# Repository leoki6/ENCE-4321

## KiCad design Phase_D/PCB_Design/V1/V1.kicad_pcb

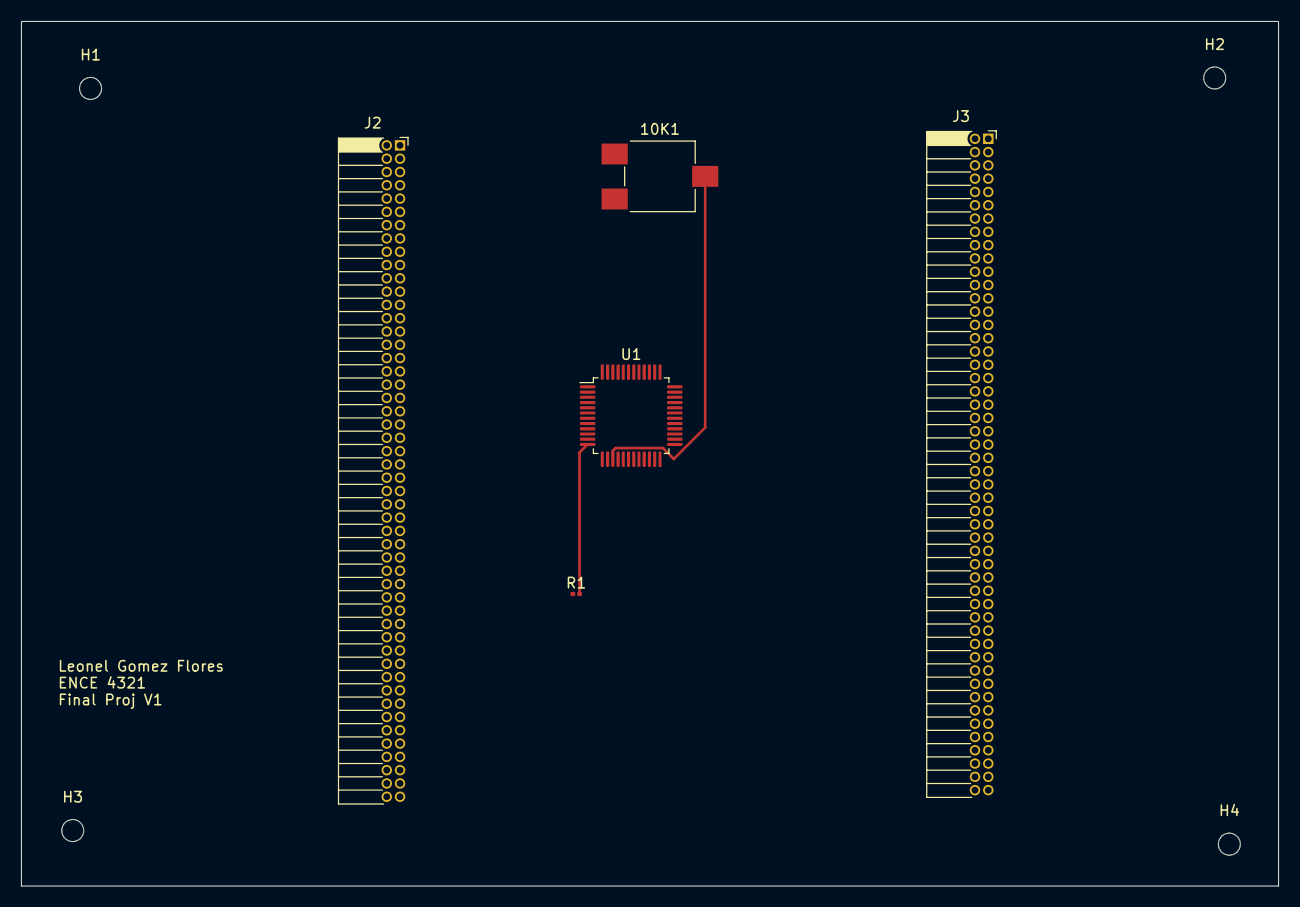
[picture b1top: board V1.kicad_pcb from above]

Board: 2 copper layers, 120.1 x 82.6 mm, 9 parts (0 on the bottom side), 2 nets.

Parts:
10K1: R_Potentiometer; Potentiometer_ACP_CA6-VSMD_Vertical
H1, H2, H3, H4: MountingHole; MountingHole_2.1mm
J2, J3: Conn_01x40_Socket; PinSocket_2x50_P1.27mm_Horizontal
R1: R; R_0201_0603Metric
U1: STM32C031C4Tx; LQFP-48_7x7mm_P0.5mm

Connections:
ADC_1: R1.2, U1.12 (PA1)
ADC_2: 10K1.2, U1.15 (PA4)

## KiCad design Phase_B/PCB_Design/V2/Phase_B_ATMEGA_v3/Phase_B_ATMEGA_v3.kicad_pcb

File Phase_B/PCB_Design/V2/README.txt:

The initial version of the folder Phase_B_ATMEGA_v3 was a template provided by Professor Martins
in ENCE-4231.

Files pertaining to the generation/creation of: housing, component placement, PCB dimensioning, Drill, Gerber, 3D Models, etc
were created by the author of this repository.

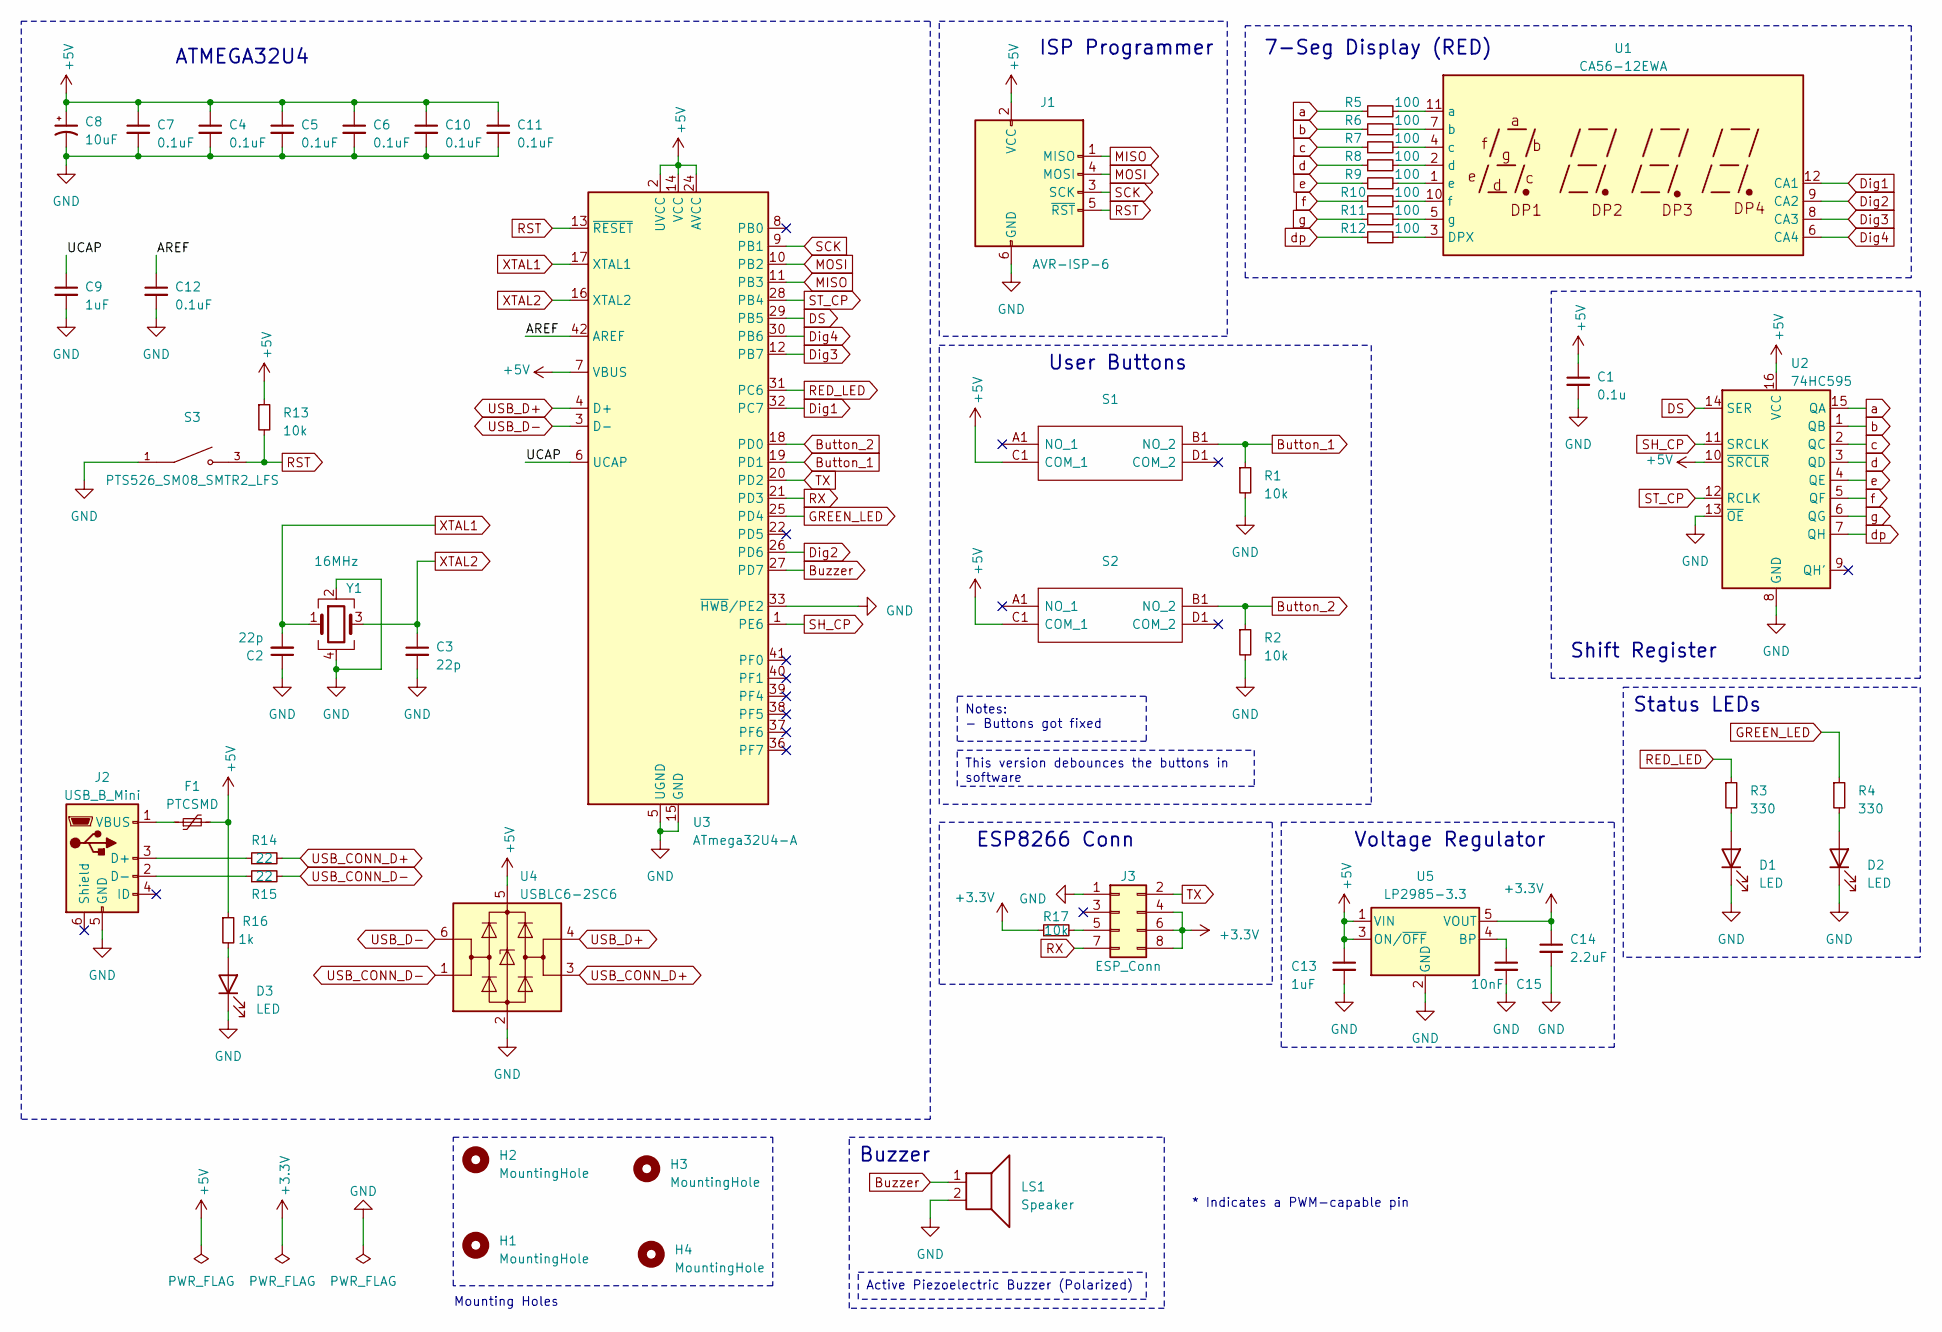
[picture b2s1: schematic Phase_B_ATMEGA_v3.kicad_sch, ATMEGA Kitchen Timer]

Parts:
C1: 0.1u; C_0603_1608Metric
C2, C3: 22p; C_0603_1608Metric
C4, C5, C6, C7, C10, C11, C12: 0.1uF; C_0603_1608Metric
C8: 10uF; C_0805_2012Metric
C9, C13: 1uF; C_0603_1608Metric
C14: 2.2uF; C_0603_1608Metric
C15: 10nF; C_0603_1608Metric
D1, D2, D3: LED; LED_0805_2012Metric
F1: PTCSMD; Fuse_1812_4532Metric
H1, H2, H3, H4: MountingHole; MountingHole_2.2mm_M2
J1: AVR-ISP-6; PinSocket_2x03_P2.54mm_Vertical
J2: USB_B_Mini; USB_Mini-B_Lumberg_2486_01_Horizontal
J3: ESP_Conn; PinSocket_2x04_P2.54mm_Vertical
LS1: Speaker; Buzzer_12x9.5RM7.6
R1, R2: 10k; R_0805_2012Metric
R3, R4: 330; R_0805_2012Metric
R5, R6, R7, R8, R9, R10, R11, R12: 100; R_0805_2012Metric
R13, R17: 10k; R_0603_1608Metric
R14, R15: 22; R_0603_1608Metric
R16: 1k; R_0603_1608Metric
S1, S2: PTS125SM43SMTR21M_LFS; PTS125_SMD_Button; Manufacturer_Part_Number PTS125SM43SMTR21M LFS; Mouser Part Number 611-PTS125S43SMTRLFS
S3: PTS526_SM08_SMTR2_LFS; PTS526_SMD_Button; PARTREV 20 mar 19
U1: CA56-12EWA
U2: 74HC595; TSSOP-16_4.4x5mm_P0.65mm
U3: ATmega32U4-A; TQFP-44_10x10mm_P0.8mm
U4: USBLC6-2SC6; SOT-23-6
U5: LP2985-3.3; SOT-23-5
Y1: 16MHz; Crystal_SMD_Abracon_ABM8G-4Pin_3.2x2.5mm

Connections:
+3.3V: C14.1, J3.4, J3.6, J3.8, R17.1, U5.5 (VOUT)
+5V: C1.1, C4.1, C5.1, C6.1, C7.1, C8.1, C10.1, C11.1, C13.1, F1.2, J1.2 (VCC), R13.1, R16.1, S1.C1 (COM_1), S2.C1 (COM_1), U2.10 (~SRCLR), U2.16 (VCC), U3.2 (UVCC), U3.7 (VBUS), U3.14 (VCC), U3.24 (AVCC), U3.34 (VCC), U3.44 (AVCC), U4.5 (VBUS), U5.1 (VIN), U5.3 (ON/~OFF)
/AREF: C12.1, U3.42 (AREF)
/UCAP: C9.1, U3.6 (UCAP)
Button_1: R1.1, S1.B1 (NO_2), U3.19 (PD1)
Button_2: R2.1, S2.B1 (NO_2), U3.18 (PD0)
Buzzer: LS1.1, U3.27 (PD7)
DS: U2.14 (SER), U3.29 (PB5)
Dig1: U1.12 (CA1), U3.32 (PC7)
Dig2: U1.9 (CA2), U3.26 (PD6)
Dig3: U1.8 (CA3), U3.12 (PB7)
Dig4: U1.6 (CA4), U3.30 (PB6)
GND: C1.2, C2.1, C3.2, C4.2, C5.2, C6.2, C7.2, C8.2, C9.2, C10.2, C11.2, C12.2, C13.2, C14.2, C15.2, D1.1 (K), D2.1 (K), D3.1 (K), J1.6 (GND), J2.5 (GND), J3.1, LS1.2, R1.2, R2.2, S3.1, U2.8 (GND), U2.13 (~OE), U3.5 (UGND), U3.15 (GND), U3.23 (GND), U3.33 (~HWB/PE2), U3.35 (GND), U3.43 (GND), U4.2 (GND), U5.2 (GND), Y1.2, Y1.4
GREEN_LED: R4.1, U3.25 (PD4)
MISO: J1.1 (MISO), U3.11 (PB3)
MOSI: J1.4 (MOSI), U3.10 (PB2)
unnamed: D1.2 (A), R3.2
unnamed: D2.2 (A), R4.2
unnamed: D3.2 (A), R16.2
unnamed: J2.3 (D+), R14.1
unnamed: J2.2 (D-), R15.1
unnamed: F1.1, J2.1 (VBUS)
unnamed: J3.5, R17.2
unnamed: R12.2, U1.3 (DPX)
unnamed: R5.2, U1.11 (a)
unnamed: R6.2, U1.7 (b)
unnamed: R7.2, U1.4 (c)
unnamed: R8.2, U1.2 (d)
unnamed: R9.2, U1.1 (e)
unnamed: R10.2, U1.10 (f)
unnamed: R11.2, U1.5 (g)
unnamed: C15.1, U5.4 (BP)
RED_LED: R3.1, U3.31 (PC6)
RST: J1.5 (~RST), R13.2, S3.3, U3.13 (~RESET)
RX: J3.7, U3.21 (PD3)
SCK: J1.3 (SCK), U3.9 (PB1)
SH_CP: U2.11 (SRCLK), U3.1 (PE6)
ST_CP: U2.12 (RCLK), U3.28 (PB4)
TX: J3.2, U3.20 (PD2)
USB_CONN_D+: R14.2, U4.3 (I/O2)
USB_CONN_D-: R15.2, U4.1 (I/O1)
USB_D+: U3.4 (D+), U4.4 (I/O2)
USB_D-: U3.3 (D-), U4.6 (I/O1)
XTAL1: C2.2, U3.17 (XTAL1), Y1.1
XTAL2: C3.1, U3.16 (XTAL2), Y1.3
a: R5.1, U2.15 (QA)
b: R6.1, U2.1 (QB)
c: R7.1, U2.2 (QC)
d: R8.1, U2.3 (QD)
dp: R12.1, U2.7 (QH)
e: R9.1, U2.4 (QE)
f: R10.1, U2.5 (QF)
g: R11.1, U2.6 (QG)

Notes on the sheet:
Notes: - Buttons got fixed
Active Piezoelectric Buzzer (Polarized)
This version debounces the buttons in software
Shift Register
Mounting Holes
Voltage Regulator
Status LEDs
ATMEGA32U4
User Buttons
Buzzer
* Indicates a PWM-capable pin
7-Seg Display (RED)
ISP Programmer
ESP8266 Conn

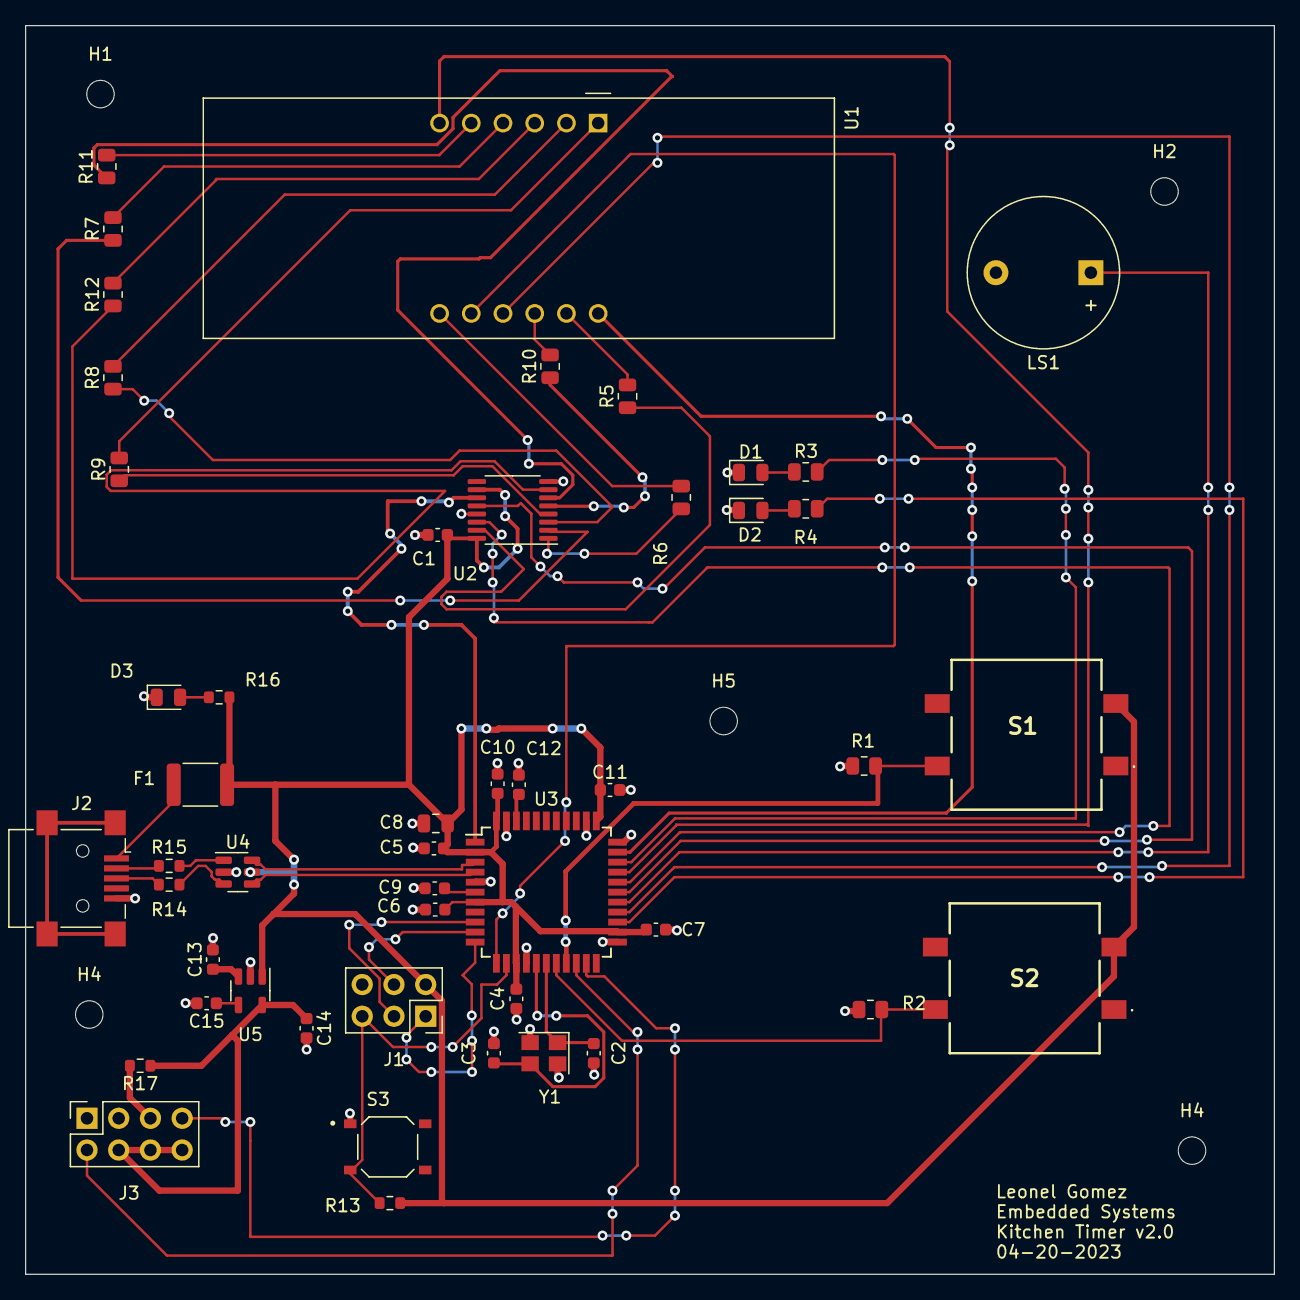
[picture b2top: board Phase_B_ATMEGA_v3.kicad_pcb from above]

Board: 2 copper layers, 100.0 x 100.0 mm, 54 parts (0 on the bottom side), 53 nets.

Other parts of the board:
H4#2, H5: MountingHole; MountingHole_2.2mm_M2

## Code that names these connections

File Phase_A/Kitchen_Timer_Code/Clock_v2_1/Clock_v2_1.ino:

#define BUTTON_2  2  // Inc Timer
#define BUTTON_1  3  // Start/Stop Timer and Stop Buzzer
#define GREEN_LED 4
#define RED_LED   5
#define BUZZER    6

#define DATA      9 // DS
#define LATCH     8 // ST_CP
#define CLOCK     7 // SH_CP

#define DIGIT_4   10
#define DIGIT_3   11
#define DIGIT_2   12
#define DIGIT_1   13

// 7-Seg Display Variables
unsigned char gtable[]=
{0x3f,0x06,0x5b,0x4f,0x66,0x6d,0x7d,0x07,0x7f,0x6f,0x77,0x7c
,0x39,0x5e,0x79,0x71,0x00};
byte gCurrentDigit;

// Volatile Variables
volatile unsigned char gISRFlag1   = 0;
volatile unsigned char gBuzzerFlag = 0;

// Timer Variables
#define DEFAULT_COUNT 30     // default value is 30secs
volatile int  gCount        = DEFAULT_COUNT;
unsigned char gTimerRunning = 0; 

unsigned int gReloadTimer1 = 62500; // corresponds to 1 second
byte         gReloadTimer2 = 10;  // display refresh time

/**
 * @brief Setup peripherals and timers
 * @param
 * @return
 */
void setup() {
  // LEDs Pins
  pinMode(RED_LED, OUTPUT);
  pinMode(GREEN_LED, OUTPUT);

  // LEDs -> Timer Stopped
  digitalWrite(RED_LED, HIGH);
  digitalWrite(GREEN_LED, HIGH);

  // Button Pins
  pinMode(BUTTON_1, INPUT_PULLUP);
  attachInterrupt(digitalPinToInterrupt(BUTTON_1), buttonISR1, RISING);
  pinMode(BUTTON_2, INPUT_PULLUP);
  attachInterrupt(digitalPinToInterrupt(BUTTON_2), buttonISR2, RISING);

  // Buzer Pins
  pinMode(BUZZER, OUTPUT);

  // Buzzer -> Off
  digitalWrite(BUZZER,LOW);

  // 7-Seg Display
  pinMode(DIGIT_1, OUTPUT);
  pinMode(DIGIT_2, OUTPUT);
  pinMode(DIGIT_3, OUTPUT);
  pinMode(DIGIT_4, OUTPUT);

  // Shift Register Pins
  pinMode(LATCH, OUTPUT);
  pinMode(CLOCK, OUTPUT);
  pinMode(DATA, OUTPUT);

  dispOff();  // turn off the display

  // Initialize Timer1 (16bit) -> Used for clock
  // Speed of Timer1 = 16MHz/256 = 62.5 KHz
  //startTimer1(); // this is done using the start button

  // Initialize Timer2 (8bit) -> Used to refresh display
  // Speed of Timer2 = 16MHz/1024 = 15.625 KHz
  TCCR2A = 0;
  TCCR2B = 0;
  OCR2A = gReloadTimer2;                     // max value 2^8 - 1 = 255
  TCCR2A |= (1<<WGM21);
  TCCR2B = (1<<CS22) | (1<<CS21) | (1<<CS20); // 1204 prescaler
  TIMSK2 |= (1<<OCIE2A);
  interrupts();                               // enable all interrupts
}

/**
 * @brief Shifts the bits through the shift register
 * @param num
 * @param dp
 * @return
 */
void display(unsigned char num, unsigned char dp)
{
  digitalWrite(LATCH, LOW);
  shiftOut(DATA, CLOCK, MSBFIRST, gtable[num] | (dp<<7));
  digitalWrite(LATCH, HIGH);
}

/**
 * @brief Turns the 7-seg display off
 * @param
 * @return
 */
void dispOff()
{
   digitalWrite(DIGIT_1, HIGH);
   digitalWrite(DIGIT_2, HIGH);
   digitalWrite(DIGIT_3, HIGH);
   digitalWrite(DIGIT_4, HIGH);
}

/**
 * @brief Button 2 ISR
 * @param
 * @return
 */
void buttonISR2()
{
  // Increment Clock
  gCount++;
}

/**
 * @brief Button 1 ISR
 * @param
 * @return
 */
void buttonISR1()
{ 
  // Set ISR Flag
  gISRFlag1 = 1;
}

/**
 * @brief Timer 2 ISR
 * @param TIMER2_COMPA_vect
 * @return
 */
ISR(TIMER2_COMPA_vect)   // Timer2 interrupt service routine (ISR)
{
  dispOff();  // turn off the display
  OCR2A = gReloadTimer2;  // load timer
 
  switch (gCurrentDigit)
  {
    case 1: //0x:xx
      display( int((gCount/60) / 10) % 6, 0 );   // prepare to display digit 1 (most left)
      digitalWrite(DIGIT_1, LOW);  // turn on digit 1
      break;
 
    case 2: //x0:xx
      display( int(gCount / 60) % 10, 1 );   // prepare to display digit 2
      digitalWrite(DIGIT_2, LOW);     // turn on digit 2
      break;
 
    case 3: //xx:0x
      display( (gCount / 10) % 6, 0 );   // prepare to display digit 3
      digitalWrite(DIGIT_3, LOW);    // turn on digit 3
      break;
 
    case 4: //xx:x0
      display(gCount % 10, 0); // prepare to display digit 4 (most right)
      digitalWrite(DIGIT_4, LOW);  // turn on digit 4
      break;

    default:
      break;
  }
 
  gCurrentDigit = (gCurrentDigit % 4) + 1;
}

/**
 * @brief Timer 1 ISR
 * @param TIMER1_COMPA_vect
 * @return
 */
ISR(TIMER1_COMPA_vect)  // Timer1 interrupt service routine (ISR)
{
  gCount--;
  OCR1A = gReloadTimer1;

  if(gCount == 0)
  {
      // Stop Timer
      stopTimer1();
      
      // Raise Alarm
      gBuzzerFlag = 1;
      gTimerRunning = 0;
  }
}

/**
 * @brief Stop Timer 1
 * @param
 * @return
 */
void stopTimer1()
{
  // Stop Timer
  TCCR1B = 0; // stop clock
  TIMSK1 = 0; // cancel clock timer interrupt
}

/**
 * @brief Start Timer 1
 * @param
 * @return
 */
void startTimer1()
{
  // Initialize Timer1 (16bit) -> Used for clock
  // Speed of Timer1 = 16MHz/256 = 62.5 KHz
  noInterrupts();
  TCCR1A = 0;
  TCCR1B = 0;
  OCR1A = gReloadTimer1; // compare match register 16MHz/256
  TCCR1B |= (1<<WGM12);   // CTC mode
  TCCR1B |= (1<<CS12);    // 256 prescaler 
  TIMSK1 |= (1<<OCIE1A);  // enable timer compare interrupt
  interrupts();
}

/**
 * @brief Turn On Buzzer
 * @param
 * @return
 */
void activeBuzzer()
{
  unsigned char i;
  unsigned char sleepTime = 1; // ms
  
  for(i=0;i<100;i++)
  {
    digitalWrite(BUZZER,HIGH);
    delay(sleepTime);//wait for 1ms
    digitalWrite(BUZZER,LOW);
    delay(sleepTime);//wait for 1ms
  }
}

/**
 * @brief Main Loop
 * @param
 * @return
 */
void loop() 
{
  // Attend Button 2 ISR
  if(gISRFlag1 == 1)
  {
    // Reset ISR Flag
    gISRFlag1 = 0;

    if(gTimerRunning == 0)
    {
      // Start Timer
      gTimerRunning = 1;

      if(gCount == 0)
        gCount = DEFAULT_COUNT;

      if(gBuzzerFlag == 1)
      {
        gBuzzerFlag = 0;

        // LEDs -> Timer Stopped
        digitalWrite(RED_LED, HIGH);
        digitalWrite(GREEN_LED, HIGH);
      }
      else
      {
        startTimer1();
        // LEDs -> Timer Running
        digitalWrite(RED_LED, LOW);
        digitalWrite(GREEN_LED, HIGH);
      }
    }
    else
    {
      // Stop Timer
      stopTimer1();
      gTimerRunning = 0;

      // LEDs -> Timer Running
      digitalWrite(RED_LED, HIGH);
      digitalWrite(GREEN_LED, HIGH);
    }
  }

  // Attend gBuzzerFlag
  if(gBuzzerFlag == 1)
  {
    // Make Noise...
    digitalWrite(RED_LED, HIGH);
    digitalWrite(GREEN_LED, LOW);
    activeBuzzer();
  }
}

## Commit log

2023-04-06 testTesting
2023-04-06 ya boi
2023-04-06 just testing again
2023-04-06 testing again
2023-04-12 Update Details: File Structure, Various files pertaining to Phase_A and B.
2023-04-12 Update for files and file structure
2023-04-12 Update: New Block Diags, PCB Files, and Programs for both Phase A & B
2023-04-16 Phase B has received a template. Phase A unchanged.
2023-04-16 Test
2023-04-16 Placement Update
2023-04-16 readme update
2023-04-16 Push Test
2023-04-16 readme for kitchen timer update
2023-04-16 Placement Tinkering
2023-04-18 Added housing files and add missing 3d models in PCB viewer for V2
2023-04-18 Routing for V2
2023-04-20 Phase B Update: Routing, BOM Files, Drill Files, Gerber Files, and Assembly PDF
2023-04-20 Extraneous File Deleted
2023-04-20 Schematic Updates, 3D Model PDFs and Images added, etc.
2023-04-24 Gerber File Update, Adjusted Board Dimension, etc.
2023-05-02 Misc. Update
2023-05-04 Folder Structure Update
2023-05-04 Structure Update
2023-05-04 Report update and program update
2023-05-05 New Report Version
2023-05-05 Report Update
2023-06-01 V1 Prototype Added for Phase D
2023-06-01 Prototype Update
2023-06-01 STM32 Code Update
2023-06-01 Supporting Doc Update
2023-06-01 Phase D Update
2023-06-01 Phase D Updates
